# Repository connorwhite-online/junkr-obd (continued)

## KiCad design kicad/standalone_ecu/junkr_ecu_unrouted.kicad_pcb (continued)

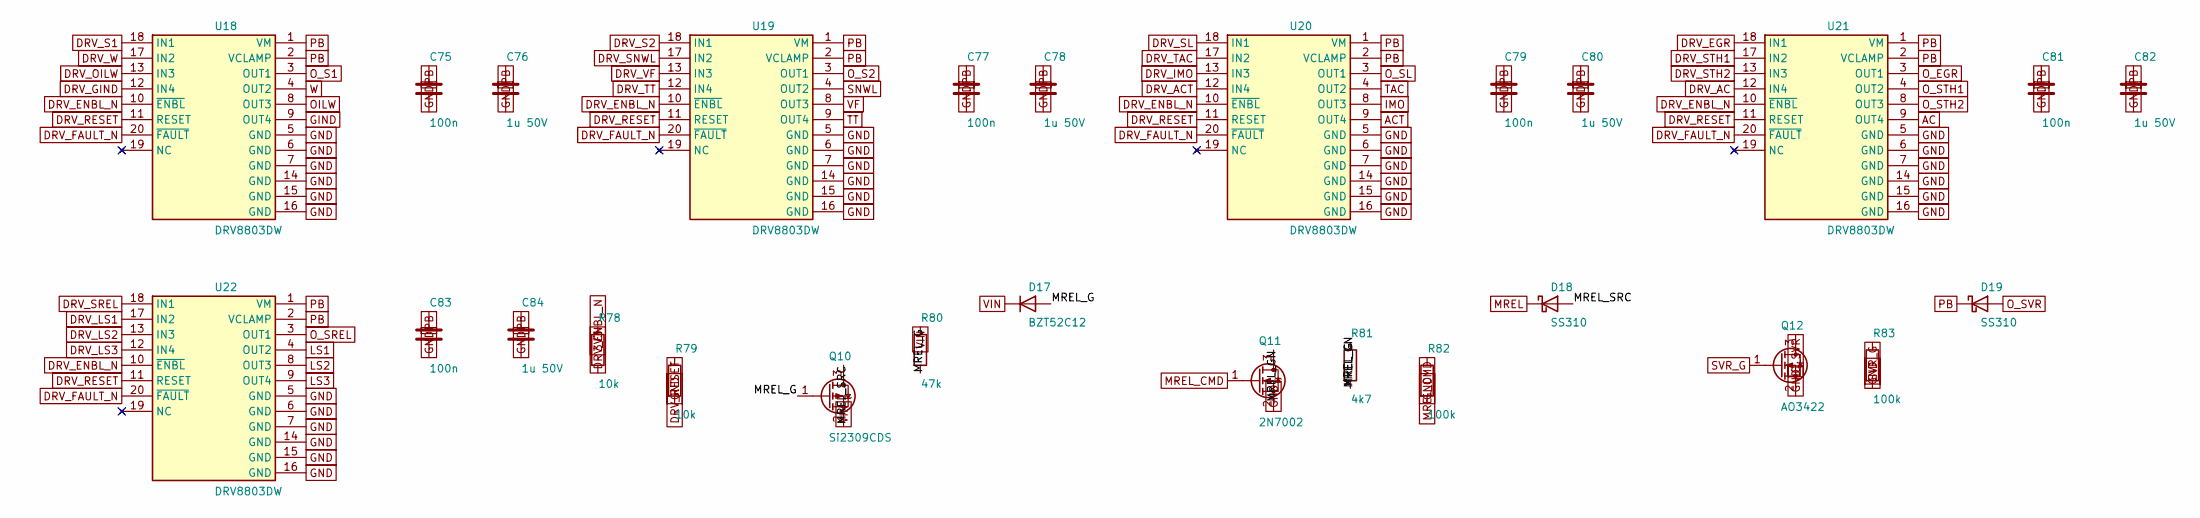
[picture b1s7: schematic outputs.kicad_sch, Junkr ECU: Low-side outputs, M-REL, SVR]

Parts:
C75, C77, C79, C81, C83: 100n; C_0603_1608Metric
C76, C78, C80, C82, C84: 1u 50V; C_0805_2012Metric
D17: BZT52C12; D_SOD-123; MPN BZT52C12
D18, D19: SS310; D_SMA; MPN SS310
Q10: Si2309CDS; SOT-23; MPN SI2309CDS-T1-GE3
Q11: 2N7002; SOT-23; MPN 2N7002
Q12: AO3422; SOT-23; MPN AO3422
R78, R79: 10k; R_0603_1608Metric
R80: 47k; R_0603_1608Metric
R81: 4k7; R_0603_1608Metric
R82, R83: 100k; R_0603_1608Metric
U18, U19, U20, U21, U22: DRV8803DW; SOIC-20W_7.5x12.8mm_P1.27mm; MPN DRV8803DWR

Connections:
3V3: R78.1; also elsewhere on the board
AC: U21.9 (OUT4); also elsewhere on the board
ACT: U20.9 (OUT4); also elsewhere on the board
DRV_AC: U21.12 (IN4); also elsewhere on the board
DRV_ACT: U20.12 (IN4); also elsewhere on the board
DRV_EGR: U21.18 (IN1); also elsewhere on the board
DRV_ENBL_N: R78.2, U18.10 (~ENBL), U19.10 (~ENBL), U20.10 (~ENBL), U21.10 (~ENBL), U22.10 (~ENBL); also elsewhere on the board
DRV_FAULT_N: U18.20 (~FAULT), U19.20 (~FAULT), U20.20 (~FAULT), U21.20 (~FAULT), U22.20 (~FAULT); also elsewhere on the board
DRV_GIND: U18.12 (IN4); also elsewhere on the board
DRV_IMO: U20.13 (IN3); also elsewhere on the board
DRV_LS1: U22.17 (IN2); also elsewhere on the board
DRV_LS2: U22.13 (IN3); also elsewhere on the board
DRV_LS3: U22.12 (IN4); also elsewhere on the board
DRV_OILW: U18.13 (IN3); also elsewhere on the board
DRV_RESET: R79.1, U18.11 (RESET), U19.11 (RESET), U20.11 (RESET), U21.11 (RESET), U22.11 (RESET); also elsewhere on the board
DRV_S1: U18.18 (IN1); also elsewhere on the board
DRV_S2: U19.18 (IN1); also elsewhere on the board
DRV_SL: U20.18 (IN1); also elsewhere on the board
DRV_SNWL: U19.17 (IN2); also elsewhere on the board
DRV_SREL: U22.18 (IN1); also elsewhere on the board
DRV_STH1: U21.17 (IN2); also elsewhere on the board
DRV_STH2: U21.13 (IN3); also elsewhere on the board
DRV_TAC: U20.17 (IN2); also elsewhere on the board
DRV_TT: U19.12 (IN4); also elsewhere on the board
DRV_VF: U19.13 (IN3); also elsewhere on the board
DRV_W: U18.17 (IN2); also elsewhere on the board
GIND: U18.9 (OUT4); also elsewhere on the board
GND: C75.2, C76.2, C77.2, C78.2, C79.2, C80.2, C81.2, C82.2, C83.2, C84.2, Q11.2 (S), Q12.2 (S), R79.2, R82.2, R83.2, U18.5 (GND), U18.6 (GND), U18.7 (GND), U18.14 (GND), U18.15 (GND), U18.16 (GND), U19.5 (GND), U19.6 (GND), U19.7 (GND), U19.14 (GND), U19.15 (GND), U19.16 (GND), U20.5 (GND), U20.6 (GND), U20.7 (GND), U20.14 (GND), U20.15 (GND), U20.16 (GND), U21.5 (GND), U21.6 (GND), U21.7 (GND), U21.14 (GND), U21.15 (GND), U21.16 (GND), U22.5 (GND), U22.6 (GND), U22.7 (GND), U22.14 (GND), U22.15 (GND), U22.16 (GND); also elsewhere on the board
IMO: U20.8 (OUT3); also elsewhere on the board
LS1: U22.4 (OUT2); also elsewhere on the board
LS2: U22.8 (OUT3); also elsewhere on the board
LS3: U22.9 (OUT4); also elsewhere on the board
MREL: D18.1 (K); also elsewhere on the board
MREL_CMD: Q11.1 (G), R82.1; also elsewhere on the board
MREL_G: D17.2 (A), Q10.1 (G), R80.2, R81.1
MREL_GN: Q11.3 (D), R81.2
MREL_SRC: D18.2 (A), Q10.3 (D)
OILW: U18.8 (OUT3); also elsewhere on the board
O_EGR: U21.3 (OUT1); also elsewhere on the board
O_S1: U18.3 (OUT1); also elsewhere on the board
O_S2: U19.3 (OUT1); also elsewhere on the board
O_SL: U20.3 (OUT1); also elsewhere on the board
O_SREL: U22.3 (OUT1); also elsewhere on the board
O_STH1: U21.4 (OUT2); also elsewhere on the board
O_STH2: U21.8 (OUT3); also elsewhere on the board
O_SVR: D19.2 (A), Q12.3 (D); also elsewhere on the board
PB: C75.1, C76.1, C77.1, C78.1, C79.1, C80.1, C81.1, C82.1, C83.1, C84.1, D19.1 (K), U18.1 (VM), U18.2 (VCLAMP), U19.1 (VM), U19.2 (VCLAMP), U20.1 (VM), U20.2 (VCLAMP), U21.1 (VM), U21.2 (VCLAMP), U22.1 (VM), U22.2 (VCLAMP); also elsewhere on the board
SNWL: U19.4 (OUT2); also elsewhere on the board
SVR_G: Q12.1 (G), R83.1; also elsewhere on the board
TAC: U20.4 (OUT2); also elsewhere on the board
TT: U19.9 (OUT4); also elsewhere on the board
VF: U19.8 (OUT3); also elsewhere on the board
VIN: D17.1 (K), Q10.2 (S), R80.1; also elsewhere on the board
W: U18.4 (OUT2); also elsewhere on the board

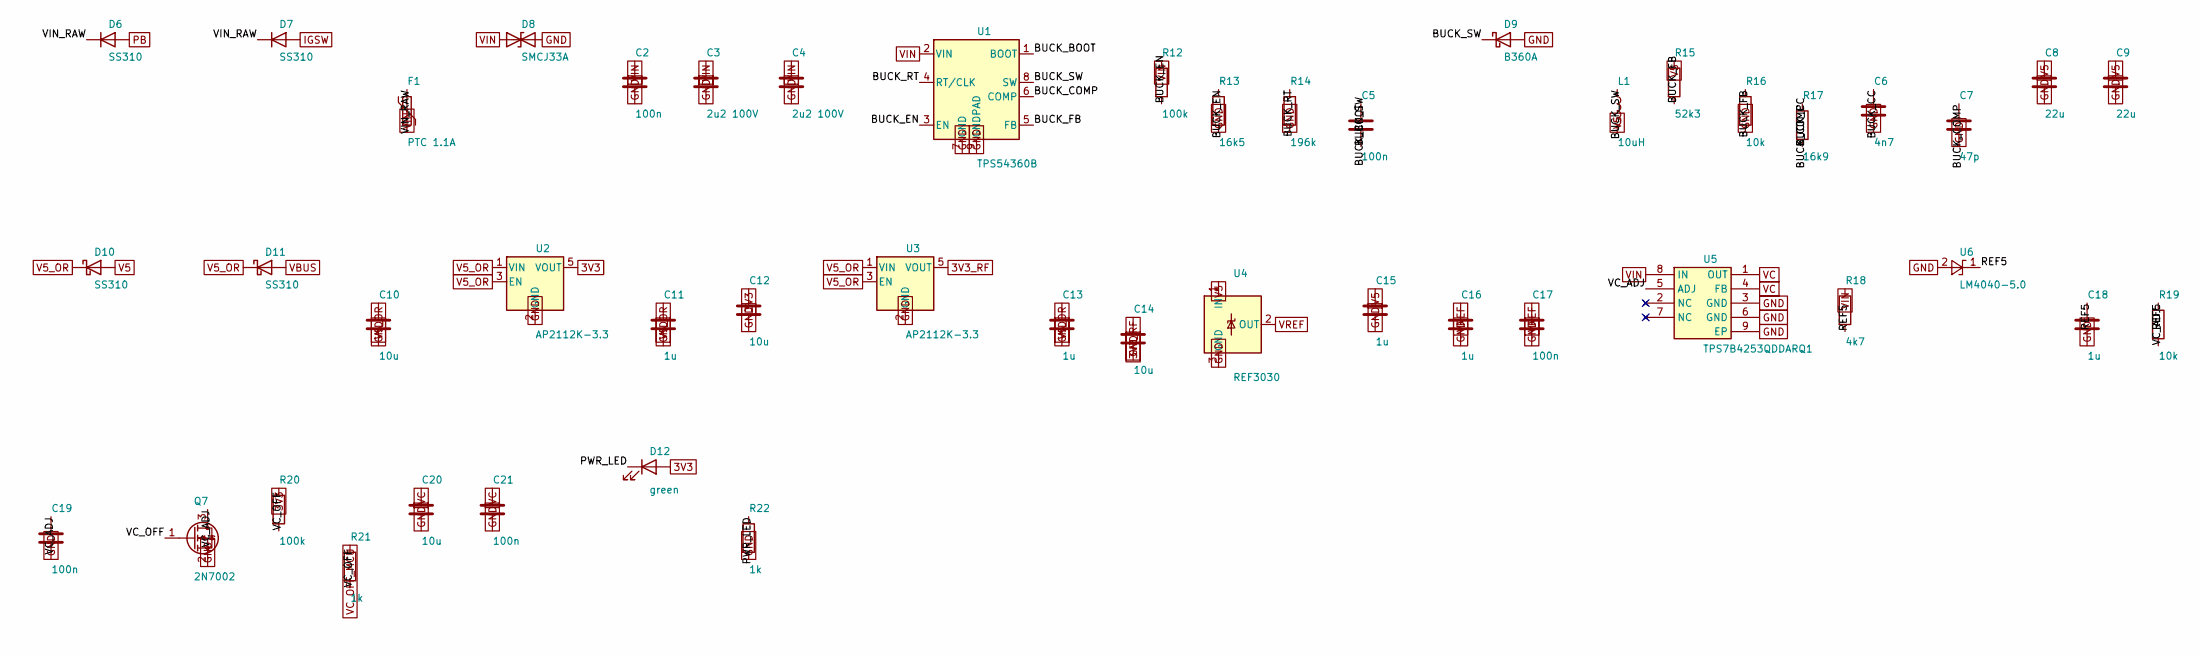
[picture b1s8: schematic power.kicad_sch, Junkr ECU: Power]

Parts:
C2, C5, C17, C19, C21: 100n; C_0603_1608Metric
C3, C4: 2u2 100V; C_1210_3225Metric
C6: 4n7; C_0603_1608Metric
C7: 47p; C_0603_1608Metric
C8, C9: 22u; C_1206_3216Metric
C10, C12, C14, C20: 10u; C_0805_2012Metric
C11, C13, C15, C16, C18: 1u; C_0603_1608Metric
D6, D7, D10, D11: SS310; D_SMA; MPN SS310
D8: SMCJ33A; D_SMC; MPN SMCJ33A
D9: B360A; D_SMA; MPN B360A-13-F
D12: green; LED_0603_1608Metric
F1: PTC 1.1A; Fuse_1812_4532Metric; MPN 1812L110/33MR
L1: 10uH; L_Sunlord_SWPA6045S; MPN SWPA6045S100MT
Q7: 2N7002; SOT-23; MPN 2N7002
R12, R20: 100k; R_0603_1608Metric
R13: 16k5; R_0603_1608Metric
R14: 196k; R_0603_1608Metric
R15: 52k3; R_0603_1608Metric
R16, R19: 10k; R_0603_1608Metric
R17: 16k9; R_0603_1608Metric
R18: 4k7; R_0603_1608Metric
R21, R22: 1k; R_0603_1608Metric
U1: TPS54360B; TI_SO-PowerPAD-8_ThermalVias; MPN TPS54360BDDAR
U2, U3: AP2112K-3.3; SOT-23-5; MPN AP2112K-3.3TRG1
U4: REF3030; SOT-23; MPN REF3030AIDBZR
U5: TPS7B4253QDDARQ1; HSOP-8-1EP_3.9x4.9mm_P1.27mm_EP2.41x3.1mm; MPN TPS7B4253QDDARQ1
U6: LM4040-5.0; SOT-23; MPN LM4040DIM3-5.0/NOPB

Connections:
3V3: C12.1, D12.2 (A), R20.1, U2.5 (VOUT); also elsewhere on the board
3V3_RF: C14.1, U3.5 (VOUT); also elsewhere on the board
BUCK_BOOT: C5.1, U1.1 (BOOT)
BUCK_CC: C6.1, R17.2
BUCK_COMP: C7.1, R17.1, U1.6 (COMP)
BUCK_EN: R12.2, R13.1, U1.3 (EN)
BUCK_FB: R15.2, R16.1, U1.5 (FB)
BUCK_RT: R14.1, U1.4 (RT/CLK)
BUCK_SW: C5.2, D9.1 (K), L1.1, U1.8 (SW)
GND: C2.2, C3.2, C4.2, C6.2, C7.2, C8.2, C9.2, C10.2, C11.2, C12.2, C13.2, C14.2, C15.2, C16.2, C17.2, C18.2, C19.2, C20.2, C21.2, D8.2 (A2), D9.2 (A), Q7.2 (S), R13.2, R14.2, R16.2, R22.2, U1.7 (GND), U1.9 (GNDPAD), U2.2 (GND), U3.2 (GND), U4.3 (GND), U5.3 (GND), U5.6 (GND), U5.9 (EP), U6.2 (A); also elsewhere on the board
IGSW: D7.2 (A); also elsewhere on the board
PB: D6.2 (A); also elsewhere on the board
PWR_LED: D12.1 (K), R22.1
REF5: C18.1, R18.2, R19.1, U6.1 (K)
V5: C8.1, C9.1, C15.1, D10.2 (A), L1.2, R15.1, U4.1 (IN); also elsewhere on the board
V5_OR: C10.1, C11.1, C13.1, D10.1 (K), D11.1 (K), U2.1 (VIN), U2.3 (EN), U3.1 (VIN), U3.3 (EN)
VBUS: D11.2 (A); also elsewhere on the board
VC: C20.1, C21.1, U5.1 (OUT), U5.4 (FB); also elsewhere on the board
VC_ADJ: C19.1, Q7.3 (D), R19.2, U5.5 (ADJ)
VC_OFF: Q7.1 (G), R20.2, R21.2
VC_OFF_MCU: R21.1; also elsewhere on the board
VIN: C2.1, C3.1, C4.1, D8.1 (A1), F1.2, R12.1, R18.1, U1.2 (VIN), U5.8 (IN); also elsewhere on the board
VIN_RAW: D6.1 (K), D7.1 (K), F1.1
VREF: C16.1, C17.1, U4.2 (OUT); also elsewhere on the board

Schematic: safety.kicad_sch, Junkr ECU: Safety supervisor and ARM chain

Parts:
C93, C94, C95, C96: 100n; C_0603_1608Metric
D24: yellow; LED_0603_1608Metric
D25: red; LED_0603_1608Metric
J11: RUN switch; JST_PH_B2B-PH-K_1x02_P2.00mm_Vertical
J12: UPDI; PinHeader_1x03_P2.54mm_Vertical
Q17: 2N7002; SOT-23; MPN 2N7002
R99, R100, R101: 100k; R_0603_1608Metric
R102: 10k; R_0603_1608Metric
R103, R104, R105, R106, R107: 1k; R_0603_1608Metric
U29, U30, U31: 74LVC1G08; SOT-23-5; MPN SN74LVC1G08DBVR
U32: ATtiny1616-SN; SOIC-20W_7.5x12.8mm_P1.27mm; MPN ATTINY1616-SNR

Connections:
3V3: C93.1, C94.1, C95.1, C96.1, D24.2 (A), J12.1, R103.1, R107.1, U29.5 (VCC), U30.5 (VCC), U31.5 (VCC), U32.1 (VCC); also elsewhere on the board
ARM: Q17.1 (G), U30.4, U31.2, U32.4 (PA6); also elsewhere on the board
ARM1: U29.4, U30.1
ARM_LED_A: D25.2 (A), R107.2
ARM_LED_K: D25.1 (K), Q17.3 (D)
ARM_REQ: R99.1, U29.1; also elsewhere on the board
ESP_UPDI: R105.2; also elsewhere on the board
GND: C93.2, C94.2, C95.2, C96.2, J12.3, Q17.2 (S), R99.2, R100.2, R101.2, R102.2, U29.3 (GND), U30.3 (GND), U31.3 (GND), U32.20 (GND); also elsewhere on the board
HB: U32.2 (PA4); also elsewhere on the board
NE_DIG: U32.17 (PA1); also elsewhere on the board
RUN_PWR: J11.1, R103.2
RUN_SW: J11.2, R102.1, U30.2; also elsewhere on the board
SAFE_OK: R100.1, R104.2, U29.2; also elsewhere on the board
SAFE_OK_T: R104.1, U32.5 (PA7)
SPV_CMP: U32.19 (PA3); also elsewhere on the board
SPV_IN: U32.18 (PA2); also elsewhere on the board
SVR_CMD: R101.1, U31.1; also elsewhere on the board
SVR_G: U31.4; also elsewhere on the board
TDC_DIG: U32.3 (PA5); also elsewhere on the board
TINY_LED: R106.1, U32.6 (PB5)
TINY_LED_K: D24.1 (K), R106.2
TINY_RX: U32.8 (PB3); also elsewhere on the board
TINY_TX: U32.9 (PB2); also elsewhere on the board
UPDI: J12.2, R105.1, U32.16 (~RESET/PA0)

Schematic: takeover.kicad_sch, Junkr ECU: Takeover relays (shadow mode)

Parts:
C1: 1u; C_0805_2012Metric
D1, D2, D3, D4: 1N4148W; D_SOD-123; MPN 1N4148W
D5: BZT52C12; D_SOD-123; MPN BZT52C12
K1, K2, K3: G5LE-1-DC12; Relay_SPDT_Omron-G5LE-1; MPN G5LE-1 DC12
K4, K5, K6, K7: G5V-2-H1-DC12; Relay_DPDT_Omron_G5V-2; MPN G5V-2-H1 DC12
Q1, Q2, Q3, Q4, Q6: 2N7002; SOT-23; MPN 2N7002
Q5: Si2309CDS; SOT-23; MPN SI2309CDS-T1-GE3
R2, R4, R6, R8: 1k; R_0603_1608Metric
R3, R5, R7, R9: 100k; R_0603_1608Metric
R10: 47k; R_0603_1608Metric
R11: 4k7; R_0603_1608Metric

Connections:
ARM: Q6.1 (G); also elsewhere on the board
GND: C1.2, Q1.2 (S), Q2.2 (S), Q3.2 (S), Q4.2 (S), Q6.2 (S), R3.2, R5.2, R7.2, R9.2; also elsewhere on the board
H_EGR: K6.4; also elsewhere on the board
H_S1: K4.4; also elsewhere on the board
H_S2: K4.13; also elsewhere on the board
H_SL: K5.4; also elsewhere on the board
H_SPV: K1.1; also elsewhere on the board
H_SREL: K7.13; also elsewhere on the board
H_STH1: K6.13; also elsewhere on the board
H_STH2: K7.4; also elsewhere on the board
H_SVR: K2.1; also elsewhere on the board
H_TCV: K3.1; also elsewhere on the board
K_AIR: R8.1; also elsewhere on the board
K_AIR_G: Q4.1 (G), R8.2, R9.1
K_AIR_N: D4.2 (A), K6.16, K7.16, Q4.3 (D); also elsewhere on the board
K_FUEL: R2.1; also elsewhere on the board
K_FUEL_G: Q1.1 (G), R2.2, R3.1
K_FUEL_N: D1.2 (A), K1.5, K2.5, Q1.3 (D); also elsewhere on the board
K_TIME: R4.1; also elsewhere on the board
K_TIME_G: Q2.1 (G), R4.2, R5.1
K_TIME_N: D2.2 (A), K3.5, Q2.3 (D); also elsewhere on the board
K_TRANS: R6.1; also elsewhere on the board
K_TRANS_G: Q3.1 (G), R6.2, R7.1
K_TRANS_N: D3.2 (A), K4.16, K5.16, Q3.3 (D); also elsewhere on the board
O_EGR: K6.8; also elsewhere on the board
O_S1: K4.8; also elsewhere on the board
O_S2: K4.9; also elsewhere on the board
O_SL: K5.8; also elsewhere on the board
O_SPV: K1.3; also elsewhere on the board
O_SREL: K7.9; also elsewhere on the board
O_STH1: K6.9; also elsewhere on the board
O_STH2: K7.8; also elsewhere on the board
O_SVR: K2.3; also elsewhere on the board
O_TCV: K3.3; also elsewhere on the board
S_EGR: K6.6; also elsewhere on the board
S_S1: K4.6; also elsewhere on the board
S_S2: K4.11; also elsewhere on the board
S_SL: K5.6; also elsewhere on the board
S_SPV: K1.4; also elsewhere on the board
S_SREL: K7.11; also elsewhere on the board
S_STH1: K6.11; also elsewhere on the board
S_STH2: K7.6; also elsewhere on the board
S_SVR: K2.4; also elsewhere on the board
S_TCV: K3.4; also elsewhere on the board
VIN: D5.1 (K), Q5.2 (S), R10.1; also elsewhere on the board
VRLY: C1.1, D1.1 (K), D2.1 (K), D3.1 (K), D4.1 (K), K1.2, K2.2, K3.2, K4.1, K5.1, K6.1, K7.1, Q5.3 (D); also elsewhere on the board
VRLY_G: D5.2 (A), Q5.1 (G), R10.2, R11.1
VRLY_GN: Q6.3 (D), R11.2

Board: 6 copper layers, 357 parts (0 on the bottom side), 350 nets, no tracks yet.

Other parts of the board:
H1, H2, H3, H4: MountingHole_3.2mm_M3

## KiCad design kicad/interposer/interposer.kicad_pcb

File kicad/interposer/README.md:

# PCB interposer (rev C, draft)

One 2-layer board that plugs in between the ECU and all three harness
plugs (E5, E6, E8), with an ESP32-S3-DevKitC-1 soldered on. Solder it on
the bench, plug it in, plug a USB-C cable into the DevKitC. It replaces the
printed plug + chamber + shroud stacks, the tap box and the Dupont leads.
The why and the trade-offs are in
[`docs/PCB_INTERPOSER.md`](../../docs/PCB_INTERPOSER.md).

| Top (harness edge up) | Back (mirrored) |
| --- | --- |
|  |  |

- **J1: TE 176122-6**, the ECU's own right-angle header, used whole. All
  three harness plugs click into it.
- **J2 to J4: tail pads** for the 150 mm wires of the E8, E6 and E5
  female plugs that go into the ECU. Upper-row tails land on the row
  nearer the header.
- **64 pass-throughs.** Every header pin runs straight to its tail pad on
  both copper layers. Nothing else touches 47 of them, including the
  spill valve and timing valve drives (SPV, TCV), which are never tapped.
- **17 dividers on the back.** Each is a 100k top resistor and a bottom
  resistor of 82k, 18k, 27k or 150k, with an optional 10 nF cap.
- **U1: ESP32-S3-DevKitC-1 N16R8** on its own pin headers, in the L-shaped
  end of the board. The antenna end has no copper under it. The USB end
  sticks out next to the harness plugs, so a cable plugs straight in.
  TAP_GND is the ESP32's ground and never connects to the ECU's grounds.
- **Board:** 158.5 × 63 mm overall, L-shaped (the harness plugs sit in the
  notch), 2 oz copper.

## U1 pinout

The 12 stage 1 channels keep the GPIO map from
[`docs/BUILD_STAGES.md`](../../docs/BUILD_STAGES.md).

| Pin | Signal | Bottom R | GPIO | | Pin | Signal | Bottom R | GPIO |
| --- | --- | --- | --- | --- | --- | --- | --- | --- |
| E6-2 | PIM (boost) | 82k | 1 | | E8-12 | +B (battery) | 18k | 9 |
| E6-4 | THW (coolant) | 82k | 2 | | E8-5 | W (check engine) | 27k | 3 |
| E6-3 | THA (intake air) | 82k | 4 | | E8-18 | TAC (rpm) | 27k | 11 |
| E6-5 | THF (fuel temp) | 82k | 5 | | E8-9 | SP1 (speed) | 150k | 12 |
| E6-13 | THO (ATF temp) | 82k | 6 | | E5-1 | SL (lock-up solenoid) | 27k | 13 |
| E6-11 | VA (pedal) | 82k | 7 | | E5-2 | S1 (shift solenoid 1) | 27k | 14 |
| E6-1 | VC (5 V ref) | 82k | 8 | | E5-15 | S2 (shift solenoid 2) | 27k | 15 |
| E6-9 | E2 (sensor ground) | 82k | 10 | | E5-7 | L4 (transfer low) | 27k | 16 |
| | | | | | E5-8 | TFN (transfer neutral) | 27k | 17 |

GPIO 1 to 10 are ADC1, which still works with Wi-Fi on. The E5 inputs are
on/off (0 or about 12 V); the 27k bottom keeps them under 3.3 V. Gear
comes from S1 + S2, lock-up from SL. The crank and pump speed sensors
(NE, TDC) pass through but aren't tapped: they need a VR conditioner.

## Files

| File | What |
| --- | --- |
| `gen_board.py` | Builds the board: outline, footprints, nets, the 64 locked pass-throughs, the divider cells, the DevKitC |
| `route.py` | Routes the 35 tap connections (a small two-layer maze router), pours TAP_GND, writes `interposer.kicad_pcb` and the footprint library |
| `export_scene.py` | Writes `hardware/ecu_interposer/cad/pcb_board_data.scad` for the 3D renders and the tray/lid CAD |
| `interposer.kicad_pcb` / `.kicad_pro` | The board (KiCad 7). It has no schematic: the netlist is the pinout CSV plus the table above |
| `junkr_interposer.pretty/` | Footprints, including the 176122-6 drawn from the measured rusEFI pad positions |
| `gerbers/` | Gerbers and the drill file, ready for JLCPCB/PCBWay (2 oz copper) |
| `bom.csv` | Parts with links |

Rebuild everything:

```sh
cd kicad/interposer
python3 gen_board.py && python3 route.py && python3 export_scene.py
kicad-cli pcb export gerbers -o gerbers/ -l F.Cu,B.Cu,F.SilkS,B.SilkS,F.Mask,B.Mask,Edge.Cuts interposer.kicad_pcb
kicad-cli pcb export drill -o gerbers/ interposer.kicad_pcb
../../hardware/ecu_interposer/cad/render_pcb.sh
```

DRC (KiCad 7, through `pcbnew.WriteDRCReport`): **0 errors, 0 unconnected.**
The only warnings left are footprint-vs-library mismatches.

## Copper

- **070 pins** (power, grounds, SPV, TCV): 1.4 mm on both layers for the
  upper row. The lower row is 0.5 to 0.8 mm per layer between pads, a few
  mm long. Order **2 oz** copper.
- **040 pins**: 1.0 mm (upper) and 0.6 mm (lower) on both layers.
- **Clearance**: 0.2 mm minimum, 0.25 mm on the pass-throughs.

## Before ordering: check these

1. **Pad numbering.** The rusEFI footprint numbers E8 = 1 to 22,
   E6 = 23 to 38 and E5 = 39 to 64, with the far row as the upper cavity
   row. That matches the Toyota numbering in `pinout_kzj95_at.csv`, but
   check it on a real header with a meter. It only moves which pins the
   dividers sit on; the pass-throughs are correct either way.
2. **DevKitC row spacing** is drawn at 22.86 mm (0.9 in) with pin 1 at the
   antenna end. Measure your DevKitC before ordering.
3. **176122-6 board pegs.** Drawn as 3.5 mm unplated holes, copied from
   the rusEFI footprint.
4. **Clearance at the ECU face.** The board stops about 4 mm short of the
   ECU's header mouth with an OEM-length plug, and the DevKitC's antenna
   end reaches 1 mm past the board edge. Measure the plug and the ECU face.
5. **Print one 1:1 paper copy** of `img/board_top.png` and lay a real
   header and DevKitC on it.

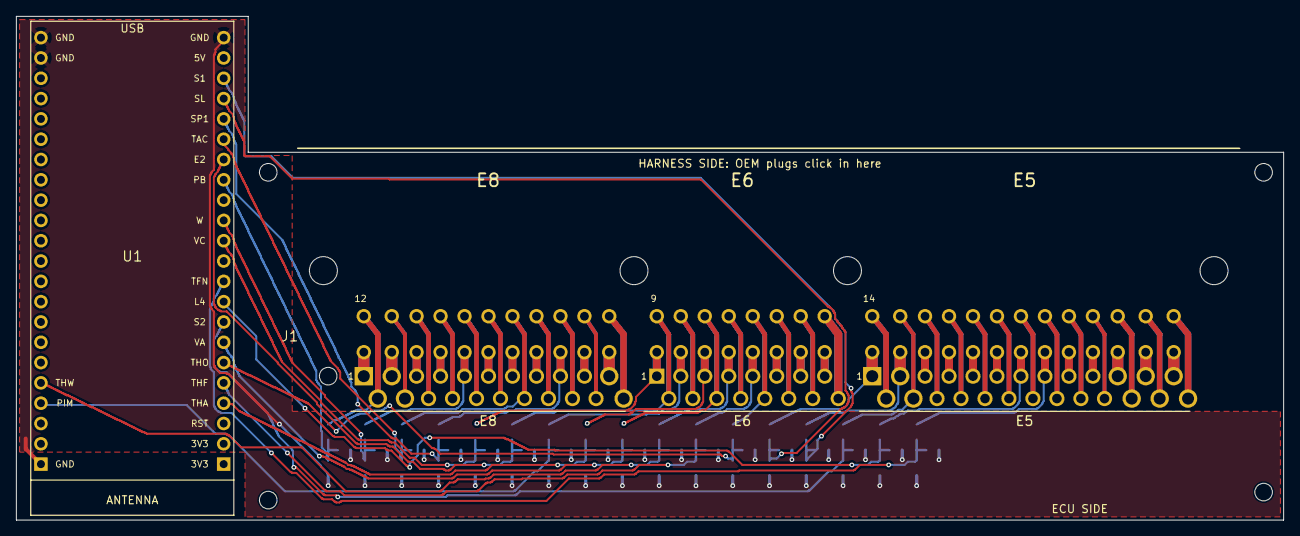
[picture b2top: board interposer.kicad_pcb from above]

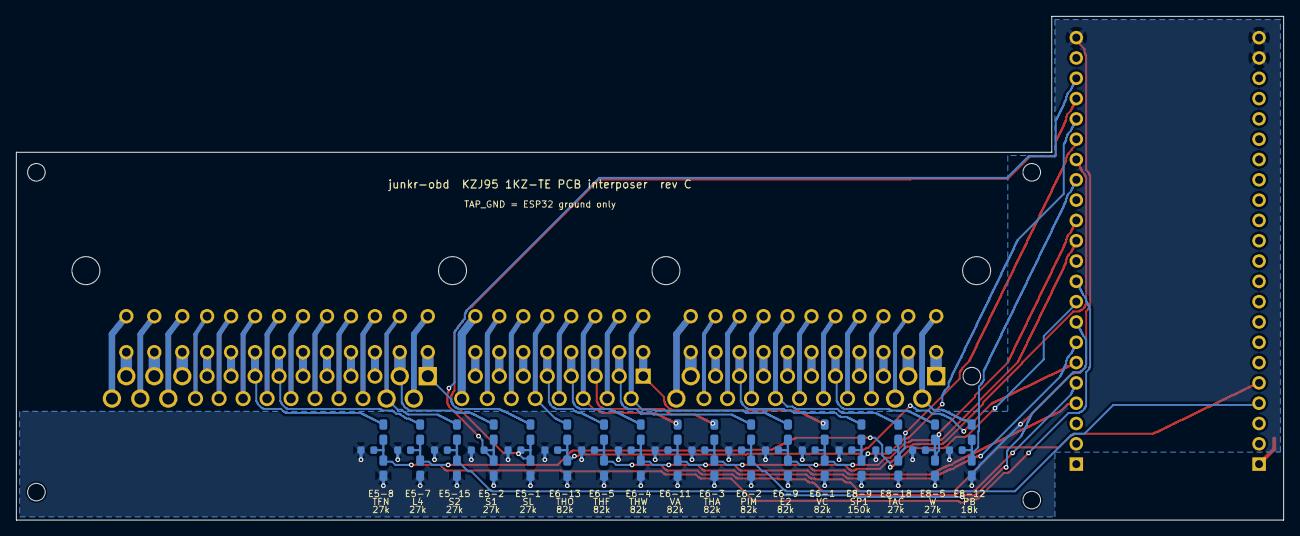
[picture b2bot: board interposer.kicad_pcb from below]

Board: 2 copper layers, 158.5 x 63.0 mm, 61 parts (51 on the bottom side), 82 nets.

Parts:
C1, C2, C3, C4, C5, C6, C7, C8, C9, C10, C11, C12, C13, C14, C15, C16, C17: 10n DNP; C_0603
H1, H2, H3, H4, H5: M2; MountingHole_2.2mm
J1: TE 176122-6; TE_176122-6_RA
J2: E8 tails (22P); Tails_E8
J3: E6 tails (16P); Tails_E6
J4: E5 tails (26P); Tails_E5
R1, R2, R3, R4, R5, R6, R7, R8, R9, R10, R11, R12, R13, R14, R15, R16, R17: 100k; R_0805
R51, R52, R54, R55, R56, R57, R58, R60: 82k; R_0805
R53, R61, R63, R64, R65, R66, R67: 27k; R_0805
R59: 18k; R_0805
R62: 150k; R_0805
U1: ESP32-S3-DevKitC-1 N16R8; ESP32S3_DevKitC1_THT

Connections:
ADC_GPIO01: C1.1, R1.2, R51.1, U1.26
ADC_GPIO02: C2.1, R2.2, R52.1, U1.27
ADC_GPIO03: C3.1, R3.2, R53.1, U1.13
ADC_GPIO04: C4.1, R4.2, R54.1, U1.4
ADC_GPIO05: C5.1, R5.2, R55.1, U1.5
ADC_GPIO06: C6.1, R6.2, R56.1, U1.6
ADC_GPIO07: C7.1, R7.2, R57.1, U1.7
ADC_GPIO08: C8.1, R8.2, R58.1, U1.12
ADC_GPIO09: C9.1, R9.2, R59.1, U1.15
ADC_GPIO10: C10.1, R10.2, R60.1, U1.16
ADC_GPIO11: C11.1, R11.2, R61.1, U1.17
ADC_GPIO12: C12.1, R12.2, R62.1, U1.18
ADC_GPIO13: C13.1, R13.2, R63.1, U1.19
ADC_GPIO14: C14.1, R14.2, R64.1, U1.20
ADC_GPIO15: C15.1, R15.2, R65.1, U1.8
ADC_GPIO16: C16.1, R16.2, R66.1, U1.9
ADC_GPIO17: C17.1, R17.2, R67.1, U1.10
E5_01_SL: J1.39, J4.1, R13.1
E5_02_S1: J1.40, J4.2, R14.1
E5_03_SP2P: J1.41, J4.3
E5_04_NEP: J1.42, J4.4
E5_05_TDCP: J1.43, J4.5
E5_06_NC: J1.44, J4.6
E5_07_L4: J1.45, J4.7, R16.1
E5_08_TFN: J1.46, J4.8, R17.1
E5_09_STH2: J1.47, J4.9
E5_10_STH1: J1.48, J4.10
E5_11_SPV: J1.49, J4.11
E5_12_TCV: J1.50, J4.12
E5_13_E01: J1.51, J4.13
E5_14_E1: J1.52, J4.14
E5_15_S2: J1.53, J4.15, R15.1
E5_16_SP2N: J1.54, J4.16
E5_17_NEN: J1.55, J4.17
E5_18_TDCN: J1.56, J4.18
E5_19_NC: J1.57, J4.19
E5_20_L: J1.58, J4.20
E5_21_2: J1.59, J4.21
E5_22_SNWL: J1.60, J4.22
E5_23_SNW: J1.61, J4.23
E5_24_EGR: J1.62, J4.24
E5_25_NC: J1.63, J4.25
E5_26_E02: J1.64, J4.26
E6_01_VC: J1.23, J3.1, R8.1
E6_02_PIM: J1.24, J3.2, R1.1
E6_03_THA: J1.25, J3.3, R4.1
E6_04_THW: J1.26, J3.4, R2.1
E6_05_THF: J1.27, J3.5, R5.1
E6_06_VRP: J1.28, J3.6
E6_07_TE2: J1.29, J3.7
E6_08_VF: J1.30, J3.8
E6_09_E2: J1.31, J3.9, R10.1
E6_10_NC: J1.32, J3.10
E6_11_VA: J1.33, J3.11, R7.1
E6_12_IDL: J1.34, J3.12
E6_13_THO: J1.35, J3.13, R6.1
E6_14_VRT: J1.36, J3.14
E6_15_TE1: J1.37, J3.15
E6_16_TT: J1.38, J3.16
E8_01_BATT: J1.1, J2.1
E8_02_SNREL: J1.2, J2.2
E8_03_MNREL: J1.3, J2.3
E8_04_STP: J1.4, J2.4
E8_05_W: J1.5, J2.5, R3.1
E8_06_OILNW: J1.6, J2.6
E8_07_GNIND: J1.7, J2.7
E8_08_IMO: J1.8, J2.8
E8_09_SP1: J1.9, J2.9, R12.1
E8_10_AC: J1.10, J2.10
E8_11_STA: J1.11, J2.11
E8_12_PB: J1.12, J2.12, R9.1
E8_13_SVR: J1.13, J2.13
E8_14_IGSW: J1.14, J2.14
E8_15_P: J1.15, J2.15
E8_16_OD2: J1.16, J2.16
E8_17_IMI: J1.17, J2.17
E8_18_TAC: J1.18, J2.18, R11.1
E8_19_ACT: J1.19, J2.19
E8_20_HSW: J1.20, J2.20
E8_21_NC: J1.21, J2.21
E8_22_NSW: J1.22, J2.22
TAP_GND: C1.2, C2.2, C3.2, C4.2, C5.2, C6.2, C7.2, C8.2, C9.2, C10.2, C11.2, C12.2, C13.2, C14.2, C15.2, C16.2, C17.2, R51.2, R52.2, R53.2, R54.2, R55.2, R56.2, R57.2, R58.2, R59.2, R60.2, R61.2, R62.2, R63.2, R64.2, R65.2, R66.2, R67.2, U1.22, U1.23, U1.43, U1.44

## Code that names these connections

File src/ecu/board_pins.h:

// Generated by kicad/standalone_ecu/tools/gen_pins.py from circuit.py. Do not edit.
// STM32H743ZIT6 (U100) pin map for the JUNKR standalone ECU rev A.
#pragma once
#include <stdint.h>

namespace board {

struct Pin { char port; uint8_t num; const char *af; };

constexpr Pin PIM_A        = {'A',  0, "ADC"};
constexpr Pin VA_A         = {'A',  3, "ADC"};
constexpr Pin THW_A        = {'A',  4, "ADC"};
constexpr Pin THA_A        = {'A',  5, "ADC"};
constexpr Pin THF_A        = {'A',  6, "ADC"};
constexpr Pin THO_A        = {'A',  7, "ADC"};
constexpr Pin STM_TX       = {'A',  9, "USART1_TX"};
constexpr Pin STM_RX       = {'A', 10, "USART1_RX"};
constexpr Pin SWDIO        = {'A', 13, "DEBUG_JTMS-SWDIO"};
constexpr Pin SWCLK        = {'A', 14, "DEBUG_JTCK-SWCLK"};
constexpr Pin NE_DIG       = {'A', 15, "TIM2_CH1"};
constexpr Pin ISPV         = {'B',  0, "COMP1_INP"};
constexpr Pin VRP_A        = {'B',  1, "ADC"};
constexpr Pin TDC_DIG      = {'B',  3, "TIM2_CH2"};
constexpr Pin LED_RUN      = {'B',  4, nullptr};
constexpr Pin LED_FAULT    = {'B',  5, nullptr};
constexpr Pin STM_IRQ      = {'B',  6, nullptr};
constexpr Pin SPV_CMP      = {'B', 10, "TIM2_CH3"};
constexpr Pin TCV_CMP      = {'B', 11, "TIM2_CH4"};
constexpr Pin SPI_CS       = {'B', 12, "SPI2_NSS"};
constexpr Pin SPI_SCK      = {'B', 13, "SPI2_SCK"};
constexpr Pin SPI_MISO     = {'B', 14, "SPI2_MISO"};
constexpr Pin SPI_MOSI     = {'B', 15, "SPI2_MOSI"};
constexpr Pin VRT_A        = {'C',  0, "ADC"};
constexpr Pin VC_A         = {'C',  1, "ADC"};
constexpr Pin E2_A         = {'C',  4, "ADC"};
constexpr Pin AUX1_A       = {'C',  5, "ADC"};
constexpr Pin TCV_CMD      = {'C',  6, "TIM8_CH1"};
constexpr Pin CAN_RX       = {'D',  0, "FDCAN1_RX"};
constexpr Pin CAN_TX       = {'D',  1, "FDCAN1_TX"};
constexpr Pin K_FUEL       = {'D',  3, nullptr};
constexpr Pin K_TIME       = {'D',  4, nullptr};
constexpr Pin K_TRANS      = {'D',  5, nullptr};
constexpr Pin K_AIR        = {'D',  6, nullptr};
constexpr Pin SVR_CMD      = {'D',  7, nullptr};
constexpr Pin MREL_CMD     = {'D',  8, nullptr};
constexpr Pin VC_OFF_MCU   = {'D',  9, nullptr};
constexpr Pin PU_EN        = {'D', 10, nullptr};
constexpr Pin ARM_REQ      = {'D', 11, nullptr};
constexpr Pin SP2_DIG      = {'D', 12, "TIM4_CH1"};
constexpr Pin SP1_CMP      = {'D', 13, "TIM4_CH2"};
constexpr Pin TAC_CMP      = {'D', 14, "TIM4_CH3"};
constexpr Pin VRAUX_DIG    = {'D', 15, "TIM4_CH4"};
constexpr Pin DRV_LS1      = {'E',  0, nullptr};
constexpr Pin DRV_LS2      = {'E',  1, nullptr};
constexpr Pin DRV_LS3      = {'E',  2, nullptr};
constexpr Pin DRV_ENBL_N   = {'E',  4, nullptr};
constexpr Pin DRV_TAC      = {'E',  5, "TIM15_CH1"};
constexpr Pin DRV_RESET    = {'E',  6, nullptr};
constexpr Pin DRV_FAULT_N  = {'E',  7, nullptr};
constexpr Pin HB           = {'E',  8, nullptr};
constexpr Pin SPV_CMD      = {'E',  9, "TIM1_CH1"};
constexpr Pin ARM          = {'E', 10, nullptr};
constexpr Pin SPV_REC      = {'E', 11, "TIM1_CH2"};
constexpr Pin SAFE_OK      = {'E', 12, nullptr};
constexpr Pin MUX_S0       = {'F',  0, nullptr};
constexpr Pin MUX_S1       = {'F',  1, nullptr};
constexpr Pin MUX_S2       = {'F',  2, nullptr};
constexpr Pin SPV_V        = {'F',  3, "ADC"};
constexpr Pin TCV_V        = {'F',  4, "ADC"};
constexpr Pin MUXA         = {'F',  5, "ADC"};
constexpr Pin MUXB         = {'F',  6, "ADC"};
constexpr Pin MUXC         = {'F',  7, "ADC"};
constexpr Pin TBOARD       = {'F',  8, "ADC"};
constexpr Pin AUX2_A       = {'F', 11, "ADC"};
constexpr Pin ITCV         = {'F', 12, "ADC"};
constexpr Pin VB_A         = {'F', 13, "ADC"};
constexpr Pin V5_A         = {'F', 14, "ADC"};
constexpr Pin MUX_S3       = {'F', 15, nullptr};
constexpr Pin DRV_S1       = {'G',  0, nullptr};
constexpr Pin DRV_W        = {'G',  1, nullptr};
constexpr Pin DRV_OILW     = {'G',  2, nullptr};
constexpr Pin DRV_GIND     = {'G',  3, nullptr};
constexpr Pin DRV_S2       = {'G',  4, nullptr};
constexpr Pin DRV_SNWL     = {'G',  5, nullptr};
constexpr Pin DRV_VF       = {'G',  6, nullptr};
constexpr Pin DRV_TT       = {'G',  7, nullptr};
constexpr Pin DRV_SL       = {'G',  8, nullptr};
constexpr Pin DRV_IMO      = {'G',  9, nullptr};
constexpr Pin DRV_ACT      = {'G', 10, nullptr};
constexpr Pin DRV_EGR      = {'G', 11, nullptr};
constexpr Pin DRV_STH1     = {'G', 12, nullptr};
constexpr Pin DRV_STH2     = {'G', 13, nullptr};
constexpr Pin DRV_AC       = {'G', 14, nullptr};
constexpr Pin DRV_SREL     = {'G', 15, nullptr};
constexpr Pin HSE_IN       = {'H',  0, "RCC_OSC_IN"};
constexpr Pin HSE_OUT      = {'H',  1, "RCC_OSC_OUT"};

}  // namespace board

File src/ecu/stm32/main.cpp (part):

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//         CH4 harness TCV edge, all input capture: every edge has a hardware
//         timestamp, so ISR latency never shows up as angle error.
//   TIM5  32-bit, 1 MHz, output compare: SPV close / peak end / open events.
//   TIM1  CH1 (PE9) SPV gate, 20 kHz PWM: 100 % for the peak, then hold duty.
//   TIM8  CH1 (PC6) TCV PWM.
// Everything else (fuel, timing loop, A343F, safety) is ecu::Engine, the same
// code the host tests run against the simulator.
//
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static Sensors sens;

static HardwareTimer t2(TIM2), t5(TIM5), t1(TIM1), t8(TIM8);
static Uart esp_link(PA10, PA9);   // USART1 to the ESP32 (also the ROM bootloader)

constexpr float SPV_PEAK_US = 450;    // full current until the valve has pulled in [VERIFY]
constexpr float SPV_HOLD_PCT = 35;    // hold duty at 20 kHz [VERIFY on the bench, ISPV]
constexpr uint32_t TCV_HZ = 300;      // [VERIFY] stock TCV frequency, scope it in shadow mode
constexpr float SPD_PULSES_PER_KM = 2548;   // 637 rev/km x 4 pulses [VERIFY]

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static void spv_set(bool on) {
    spv_on = on;
    t1.setCaptureCompare(1, on ? 100 : 0, PERCENT_COMPARE_FORMAT);
    digitalWrite(PE11, on ? HIGH : LOW);   // SPV_REC: recirculate while held, fast decay at open
}

static void t5_ch1_isr() {   // SPV close (start of the injection window)
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}
static void tcv_cmp_isr() {
    uint32_t t = t2.getCaptureCompare(4, TICK_COMPARE_FORMAT);
    bool high = digitalRead(PB11);
    if (high) { stock_tcv_period = t - stock_tcv_rise; stock_tcv_rise = t; }
    else stock_tcv_high = t - stock_tcv_rise;
    if (stock_tcv_period) stock_tcv_duty = 100.0f * stock_tcv_high / stock_tcv_period;
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enum MuxA { IDL, STP, AC, STA, IGSW, PATTERN, OD2, IMI, ACT, HSW, NSW, L4, TFN, SHIFT_L, SHIFT_2, SNW };
static uint16_t mux_bits[3];
static void scan_muxes() {
    const uint32_t sel[4] = {PF0, PF1, PF2, PF15};
    const uint32_t in[3] = {PF5, PF6, PF7};
    uint16_t b[3] = {0, 0, 0};
    for (int ch = 0; ch < 16; ch++) {
        for (int k = 0; k < 4; k++) digitalWrite(sel[k], (ch >> k) & 1);
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
static void read_sensors() {
    scan_muxes();
    sens.va_v = harness_v(PA3);
    sens.pedal = clampf(va.at(sens.va_v), 0, 100);
    sens.idl = !mux(0, IDL);   // IDL pulls the line to E2 when the pedal is released [VERIFY polarity]
    sens.ect_v = harness_v(PA4);
    sens.ect_c = ntc.at(sens.ect_v);
    sens.map_v = harness_v(PA0);
    sens.map_kpa = pim.at(sens.map_v);
    sens.vbatt = harness_v(PF13) * (18.0f / 5.0f);   // VB_A has its own 100k/22k first
    sens.starter = mux(0, STA);
    sens.brake = mux(0, STP);
    sens.od_switch_on = !mux(0, OD2);
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    uint32_t per = spd_period;
    sens.speed_kmh = (per && micros() - spd_last < 500000) ? 3.6e9f / (per * SPD_PULSES_PER_KM) : 0;
    sens.arm_switch = mux(2, 14);   // RUN_SW
    sens.supervisor_ok = digitalRead(PE12);
}

// ---------------------------------------------------------------- outputs
static void write_outputs(const Commands &c) {
    t8.setCaptureCompare(1, (uint32_t)c.tcv_duty, PERCENT_COMPARE_FORMAT);
    digitalWrite(PD7, c.svr_on);                 // SVR_CMD (gated by ARM)
    digitalWrite(PG0, c.s1);                     // DRV_S1
    digitalWrite(PG4, c.s2);                     // DRV_S2
    digitalWrite(PG8, c.sl);                     // DRV_SL
    bool k = c.takeover;
    digitalWrite(PD3, k);                        // K_FUEL
    digitalWrite(PD4, k);                        // K_TIME
    digitalWrite(PD5, k);                        // K_TRANS
    digitalWrite(PD6, k);                        // K_AIR
    digitalWrite(PD11, c.arm_req);               // ARM_REQ
    digitalWrite(PD8, eng.ne().rpm() > 0 || sens.starter);   // MREL_CMD: hold main relay while turning
    digitalWrite(PB5, c.dtc != 0);               // LED_FAULT
}

// ---------------------------------------------------------------- link to the ESP32
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    esp_link.begin(921600);
    // VC_OFF_MCU high first: our sensor 5 V stays off until we know the
    // stock ECU is not there (it has a 100k pull-up, so it is off at reset too).
    pinMode(PD9, OUTPUT);
    digitalWrite(PD9, HIGH);
    const uint32_t outs[] = {PE11, PD7, PG0, PG4, PG8, PD3, PD4, PD5, PD6, PD11, PD8, PD10,
                             PE8, PB4, PB5, PF0, PF1, PF2, PF15, PE4, PE6};
    for (uint32_t p : outs) { pinMode(p, OUTPUT); digitalWrite(p, LOW); }
    pinMode(PE12, INPUT);   // SAFE_OK
    pinMode(PE10, INPUT);   // ARM (readback)
    analogReadResolution(12);

    // TIM2: 1 MHz timestamps on all four harness timing inputs.
    t2.setPrescaleFactor(t2.getTimerClkFreq() / 1000000);
    t2.setOverflow(0xFFFFFFFF, TICK_FORMAT);
    t2.setMode(1, TIMER_INPUT_CAPTURE_RISING, PA15);
    t2.setMode(2, TIMER_INPUT_CAPTURE_RISING, PB3);
    t2.setMode(3, TIMER_INPUT_CAPTURE_FALLING, PB10);
    t2.setMode(4, TIMER_INPUT_CAPTURE_BOTHEDGE, PB11);
    t2.attachInterrupt(1, ne_isr);
    t2.attachInterrupt(2, tdc_isr);
    t2.attachInterrupt(3, spv_cmp_isr);
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    t5.attachInterrupt(3, t5_ch3_isr);
    t5.setInterruptPriority(0, 0);

    t1.setPWM(1, PE9, 20000, 0);       // SPV gate
    t8.setPWM(1, PC6, TCV_HZ, 0);      // TCV
    t2.resume();
    t5.resume();
    attachInterrupt(digitalPinToInterrupt(PD13), spd_isr, RISING);   // SP1 (vehicle speed)

    // Shadow mode when the stock ECU is present (its VC 5 V shows up on VC_A
    // before ours is switched on); standalone takeover needs the app's unlock.
    delay(50);
    eng.set_mode(Mode::Shadow);
    if (harness_v(PC1) < 1.0f) {
        // No stock ECU: we are the only ECU, so power the sensors (VC) and
        // switch in our own 2.49k sensor pull-ups (PU_EN).
        digitalWrite(PD9, LOW);
        digitalWrite(PD10, HIGH);
        standalone = true;
    }
}
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    read_sensors();
    const Commands &c = eng.update(t2_now(), sens, 0.001f);
    write_outputs(c);
    digitalWrite(PE8, ++n & 1);   // HB to the ATtiny: it trips if this stops
    if (n % 20 == 0) report();
    if (esp_link.available()) {
        // Minimal command set from the ESP32: "T" request takeover, "S" shadow.
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
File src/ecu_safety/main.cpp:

// ATtiny1616 safety supervisor firmware. Logic lives in supervisor.h (host
// tested); this file is only the pins and timers.
//
//   PA1 NE_DIG   in   pump teeth (MAX9926 output)
//   PA2 SPV_IN   in   gated SPV command (after the ARM AND gate)
//   PA3 SPV_CMP  in   harness SPV comparator, high = valve energized
//   PA4 HB       in   STM32 heartbeat, toggled by its control loop
//   PA5 TDC_DIG  in   crank TDC (logged only)
//   PA6 ARM      in   ARM line
//   PA7 SAFE_OK  out  to the ARM AND gate (1k series, 100k pull-down)
//   PB5 LED      out  low = on: steady = OK, blinking = tripped (code)
//   PB2/PB3      USART0 to the ESP32 (status line, 115200)
//
// Build: pio run -e ecu-safety   Flash over UPDI from the ESP32 (or J12).
#include <avr/interrupt.h>
#include <avr/io.h>
#include <stdio.h>

#include "supervisor.h"

static safety::Supervisor sup;
static volatile uint8_t tick_flag;

ISR(PORTA_PORT_vect) {
    uint8_t f = PORTA.INTFLAGS;
    PORTA.INTFLAGS = f;
    if (f & PIN1_bm) sup.ne_edge();
    if (f & PIN4_bm) sup.hb_edge();
    if (f & PIN2_bm) sup.spv_level(PORTA.IN & PIN2_bm);
}

ISR(TCB0_INT_vect) {
    TCB0.INTFLAGS = TCB_CAPT_bm;
    tick_flag = 1;
}

static void uart_put(char c) {
    while (!(USART0.STATUS & USART_DREIF_bm)) {}
    USART0.TXDATAL = c;
}

int main() {
    // 20 MHz internal, no prescaler (fuse OSCCFG = 20 MHz).
    _PROTECTED_WRITE(CLKCTRL.MCLKCTRLB, 0);
    // SAFE_OK low until the supervisor says otherwise.
    PORTA.DIRSET = PIN7_bm;
    PORTA.OUTCLR = PIN7_bm;
    PORTB.DIRSET = PIN5_bm | PIN2_bm;
    PORTB.OUTSET = PIN5_bm;
    // Edges: NE rising, HB both, SPV_IN both.
    PORTA.PIN1CTRL = PORT_ISC_RISING_gc;
    PORTA.PIN4CTRL = PORT_ISC_BOTHEDGES_gc;
    PORTA.PIN2CTRL = PORT_ISC_BOTHEDGES_gc;
    // 1 kHz tick on TCB0 (periodic interrupt mode, CLK_PER/2).
    TCB0.CCMP = 10000 - 1;
    TCB0.INTCTRL = TCB_CAPT_bm;
    TCB0.CTRLA = TCB_CLKSEL_CLKDIV2_gc | TCB_ENABLE_bm;
    // USART0 115200 8N1, TX only for status.
    USART0.BAUD = (uint16_t)((64UL * 20000000UL) / (16UL * 115200UL));
    USART0.CTRLB = USART_TXEN_bm;
    // Watchdog: if this loop ever hangs, the tiny resets and SAFE_OK goes low.
    _PROTECTED_WRITE(WDT.CTRLA, WDT_PERIOD_16CLK_gc);
    sei();
    uint16_t ms = 0;
    for (;;) {
        if (!tick_flag) continue;
        tick_flag = 0;
        __asm__ __volatile__("wdr");
        bool spv_cmp = PORTA.IN & PIN3_bm;
        bool armed = PORTA.IN & PIN6_bm;
        if (sup.tick(spv_cmp, armed)) PORTA.OUTSET = PIN7_bm;
        else PORTA.OUTCLR = PIN7_bm;
        ms++;
        // LED: steady on when OK, otherwise blink the trip code.
        if (sup.safe_ok()) PORTB.OUTCLR = PIN5_bm;
        else if ((ms & 0x7F) == 0) PORTB.OUTTGL = PIN5_bm;
        if (ms >= 100) {   // 10 Hz status line: "S <ok> <trip> <rpm>"
            ms = 0;
            char buf[24];
            int n = snprintf(buf, sizeof buf, "S %u %u %u\n", sup.safe_ok(), sup.last_trip(), sup.rpm());
            for (int i = 0; i < n; i++) uart_put(buf[i]);
        }
    }
}

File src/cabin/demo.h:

// Synthetic bus traffic for bench work without the truck (build env
// cabin-demo). One 90 s loop: idle, cruise with the piggyback armed, a
// hill pull that runs EGT past the red line for a few seconds, then
// back to cruise. Frames go through the same State::ingest as real ones.
#pragma once
#include <math.h>
#include <stdint.h>

#include "can_protocol.h"

namespace demo {

constexpr uint32_t LOOP_MS = 90000;

inline float ramp(float t, float t0, float t1) {
    return t <= t0 ? 0.0f : t >= t1 ? 1.0f : (t - t0) / (t1 - t0);
}

// Fills `out` with one of every frame; returns how many. Call at ~20 Hz.
inline int frames(uint32_t now_ms, can_proto::Frame* out) {
    using namespace can_proto;
    const float t = (now_ms % LOOP_MS) / 1000.0f;
    const float wob = sinf(now_ms / 700.0f);

    // load: 0 idle, ~0.35 cruise, 1 full pull
    const float pull = ramp(t, 40, 44) * (1 - ramp(t, 56, 59));
    const float load = 0.35f * ramp(t, 8, 14) + 0.65f * pull;
    const float rpm = 750 + 1500 * ramp(t, 8, 14) + 900 * pull + 25 * wob;
    const float boost_psi = 1.5f + 11.0f * (load - 0.35f > 0 ? (load - 0.35f) / 0.65f : 0) + 2.0f * load + 0.3f * wob;
    const float baro = 101.3f;
    const float pim = baro + boost_psi * 6.894757f;
    const bool armed = t > 18;
    const float extra = armed ? 0.06f : 0.0f;
    const float pim_seen = armed ? pim * (1 + extra) : pim;
    // EGT lags load; the pull overshoots 1250 °F for ~4 s around t = 52 s.
    const float egt_f = 420 + 560 * ramp(t, 9, 20) + 330 * ramp(t, 44, 52) * (1 - ramp(t, 55, 62)) + 8 * wob;
    // Coolant climbs slowly over the first 10 minutes (not per loop), so the
    // Temps trend has something to show.
    const float thw = 80 + 8 * ramp(now_ms / 1000.0f, 0, 600) + 2.5f * ramp(t, 44, 60) * (1 - ramp(t, 70, 90));
    const float tho = 70 + 18 * ramp(t, 10, 80);

    int n = 0;
    out[n++] = pack_i16(ID_EGT, to_i16(egt_f));
    out[n++] = pack_i16(ID_MAP_PSI, to_i16(boost_psi * 10));
    out[n++] = pack(MapAbs{to_u16(pim * 10), to_u16(baro * 10), 5010, U16_INVALID});
    out[n++] = pack(TapEngine{to_u16(rpm), to_i16((4 + 6 * load) * 10), to_u16((30 + 25 * load) * 10)});
    out[n++] = pack(TapFuel{to_u16((8 + 16 * load) * 10), to_u16(load * 100 * 10), to_u16(pim)});
    out[n++] = pack(TapTemps{to_i16(thw), to_i16(28 + 14 * load), 31, to_i16(tho)});
    out[n++] = pack(Piggyback{(uint8_t)armed, to_u16(pim_seen), to_u16(load * 1000), to_i16(thw),
                              (uint8_t)(extra * 100)},
                    false, 20);
    const uint32_t dig = (load > 0.5f ? (uint32_t)DIG_LOCKUP : 0u) | DIG_S1 | DIG_S2;
    out[n++] = pack(TapStatus{to_u16(13900 + 60 * wob), to_u16(load * 900 + (rpm > 900 ? 300 : 0)), dig});
    return n;
}

}  // namespace demo

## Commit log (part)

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2022-03-04 johnny-five library added
2022-03-04 new board added
2022-03-04 led initialized on board startup
2022-03-04 sensor logic ready
2022-03-04 ignition and acc switches established
2025-11-07 initial
2025-11-07 feat: Add JNKR Gauge System project files
2025-11-07 Checkpoint before follow-up message
2025-11-07 Refactor: Add dual IAT sensors and remove oil temp/battery voltage
2025-11-07 feat: Implement DFPlayer Mini audio alerts
2025-11-07 Refactor: Replace DFPlayer with piezo buzzer for alerts
2025-11-08 docs: Add guide for migrating Nextion to Adafruit TFT
2025-11-08 feat: Add SquareLine Studio + LVGL display support
    This commit introduces support for SquareLine Studio and the LVGL graphics library, providing a Mac-compatible visual GUI design solution. It includes updated documentation, hardware configurations, 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
2025-11-08 Refactor documentation and add new guides
2025-11-08 Add documentation for Adafruit 5806 display specs
2025-11-08 Refactor: Migrate to ESP32-S3 for improved performance and display
2025-11-08 Refactor: Update docs for ESP32-S3 platform migration
2025-11-08 Refactor: Update docs for platform migration
2025-11-08 feat: Add I2C sensor module design document
    This document outlines a new design for consolidating engine bay sensors onto a single I2C interface module, significantly reducing wiring complexity and improving installation quality.
2025-11-08 feat: Add I2C sensor module option
2025-11-08 Add automotive power guide and update wiring docs
2025-11-08 Refactor: Add cigarette lighter power option for gauge install
2025-11-08 Refactor cigarette lighter wiring instructions for clarity
2025-11-08 Refactor power documentation for I2C sensor module
2025-11-08 Refactor power distribution documentation
2025-11-08 Refactor power distribution documentation for clarity
2025-11-08 Refactor: Improve sensor selection and calibration documentation
2025-11-08 Add bench testing guide for ESP32 and I2C module
2025-11-08 Refactor: Replace direct links with search terms in BOM
2025-11-11 Add OEM ECU data access documentation and examples
2025-11-12 feat: Add comprehensive documentation for adaptive ECU
2025-11-12 buncha stuff
2025-11-13 Add JDM diagnostic connector analysis documentation
2025-11-13 Add comparison of DLC3 vs Analog Intercept
2025-11-13 docs: Reassess DLC3 reading feasibility, confirm it's feasible
2025-11-13 Add documentation for DLC3 available data
2025-11-13 Add documentation for DLC3 speed analysis
2025-11-13 Add DLC3 implementation guide documentation
2025-11-13 feat: Add documentation for K-Line library research
2025-11-13 docs: Add library research findings and completion reports
2025-11-13 feat: Add DLC3 K-Line wireless communication
2025-11-13 Refactor: Improve DLC3 integration and code separation
2025-11-13 Add documentation for DLC3 connector pinout and wiring
2025-11-15 simpler implementation
2025-11-15 take two
2025-11-15 Move LVGL descriptor to repo root for LVGL Pro
2025-11-15 clean up
2025-11-17 tryin something
2025-11-17 trying
2026-05-16 docs: add BOM for current Qualia ESP32-S3 simple gauge
    Reconstructs the parts list against the current source (Qualia + MAX31855 +
    ADS1115 + thermistor + MAP) instead of the pre-cleanup Mega/Nextion design.
    Uses US supplier search links (Adafruit, Digi-Key, Mouser, RockAuto, etc.)
    and flags the MAP sensor / CS pin / display size / lib_deps mismatches that
    need to be resolved before ordering.
2026-05-16 docs: switch architecture to engine-bay MCU + CAN link
    Move MAX31855 + ADS1115 sensor reads behind their own ESP32-C3 in the
    engine bay, exchange data with the cabin Qualia over a CAN bus carried on
    a 4-pin Deutsch harness (12 V, GND, CAN_H, CAN_L) instead of running raw
    SPI/I²C through automotive wiring. Updates the block diagram, harness
    pinout, ESP32-S3 pin map, and adds the engine-bay ESP32-C3 pin map and a
    firmware-layout section to README. Refreshes BOM to add the second MCU,
2026-05-16 docs: render block / data-flow / power diagrams in Mermaid
    GitHub renders Mermaid natively in markdown — drop the ASCII art for the
    system block diagram, add a sequence diagram covering the 20 Hz read +
    CAN TX/RX loop, and a power-topology diagram showing the 12 V → buck →
    3.3 V rail in the engine bay. Also documents the proposed CAN frame
    layout (0x100 EGT, 0x101 Coolant, 0x102 MAP).
2026-05-18 firmware: split into cabin LVGL listener + engine-bay CAN publisher
    Restructures src/ into per-MCU subtrees with a shared CAN frame
    contract, and converts platformio.ini to two environments
    (cabin = Qualia ESP32-S3, engine-bay = ESP32-C3 SuperMini) selected
    via build_src_filter.
    Engine-bay firmware reads MAX31855 (SPI) and ADS1115 (I²C CH0=NTC,
    CH1=MAP) and publishes three CAN frames at 500 kbps every 50 ms.
2026-05-18 kicad: hardware specs for engine-bay + cabin shields
    Adds canonical schematic netlists, BOMs with KiCad symbol + footprint
    references, design rules (trace widths, clearances, layer stack), and
    placement/routing notes for the two PCBs.
    Engine-bay shield: ESP32-C3 SuperMini + MAX31855 + ADS1115 + TJA1051
    all on 0.1" sockets, dual buck rails (3.3 V for digital, 5 V for the
    MAP sensor), SMBJ24A TVS + polyfuse + reverse-polarity diode on the
2026-05-18 docs: bench testing guide + opt-in serial debug for engine-bay
    Walks the build up in seven stages — compile, cabin UI alone, engine-bay
    reads alone, CAN loopback, real sensors, MAP sensor calibration check,
    then PCB fab — so PCBs only get ordered after every architectural
    assumption has been validated on the bench.
    Adds a DEBUG_PRINTS build flag and a paired engine-bay-debug PIO env
    that prints sensor values to the serial monitor once per second; lets
2026-05-18 docs: bench testing BOM
    Splits the bench-rig shopping list out of BENCH_TESTING.md into a
    dedicated docs/BENCH_BOM.md with US supplier search links and rough
    costs. Organized into product-BOM parts you'll already have, bench-only
    essentials, and optional debugging gear (logic analyzer, CAN sniffer,
    bench supply) with notes on when each one actually pays off.
    Approximate bench-only total: $150-300 depending on what's already
2026-05-20 hardware: vendor Adafruit STEP models + 3D sourcing guide
    Adds the MIT-licensed Qualia ESP32-S3 (PID 5800) and ADS1115 (PID 1085)
    STEP files from Adafruit's public CAD parts repo into
    hardware/3d_models/, with attribution. The Qualia model is the one you
    build the cabin display bezel around.
    Adds docs/3D_MODELS.md: a per-BOM-item sourcing table covering which
    models are vendored here, which to download from TE / GrabCAD / SnapEDA
2026-05-20 docs: pin exact ESP32-C3 SuperMini 3D model download links
    Located a matching STEP for the SuperMini board (GrabCAD model by Ulf
    Hille, also packaged in the mrtnvgr/KiCad_ESP32-C3-SuperMini repo).
    Recording the direct links rather than vendoring the file: the GitHub
    repo carries no license and the model derives from a GrabCAD upload
    whose Community License prohibits redistribution. Free to download
    directly.
